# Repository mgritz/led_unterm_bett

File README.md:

# led_unterm_bett
PCB for ESP8266-based LED Low-Lights Controller

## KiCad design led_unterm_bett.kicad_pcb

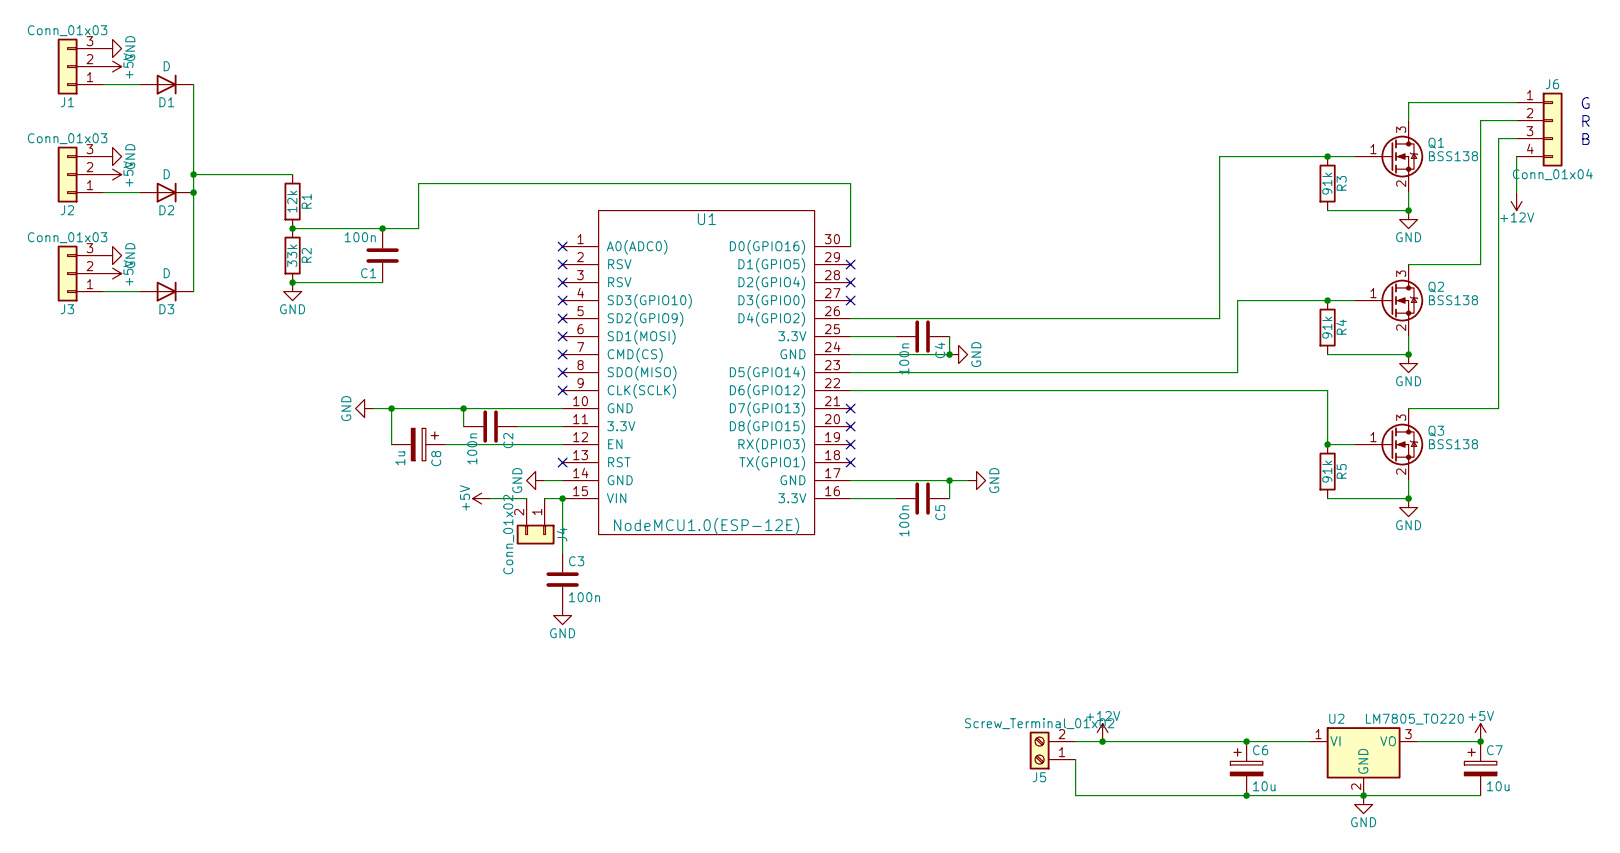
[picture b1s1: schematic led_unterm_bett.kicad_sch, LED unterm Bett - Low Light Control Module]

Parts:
C1, C2, C3, C4, C5: 100n; C_0805_HandSoldering
C6, C7: 10u; CP_Radial_D10.0mm_P3.50mm
C8: 1u; CP_Radial_D10.0mm_P3.50mm
D1, D2, D3: D; D_MiniMELF_Handsoldering
J1, J2, J3: Conn_01x03; Pin_Header_Straight_1x03_Pitch2.54mm
J4: Conn_01x02; Pin_Header_Straight_1x02_Pitch2.54mm
J5: Screw_Terminal_01x02; TerminalBlock_bornier-2_P5.08mm
J6: Conn_01x04; Pin_Header_Straight_1x04_Pitch2.54mm
Q1, Q2, Q3: BSS138; SOT-23
R1: 12k; R_0805_HandSoldering
R2: 33k; R_0805_HandSoldering
R3, R4, R5: 91k; R_0805_HandSoldering
U1: NodeMCU1.0(ESP-12E); ESP12F-Devkit-V3
U2: LM7805_TO220; TO-220-3_Vertical

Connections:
+5V: C7.1, J1.2, J2.2, J3.2, J4.2, U2.3 (VO)
+12V: C6.1, J5.2, J6.4, U2.1 (VI)
GND: C1.1, C2.2, C3.2, C4.1, C5.1, C6.2, C7.2, C8.2, J1.3, J2.3, J3.3, J5.1, Q1.2 (S), Q2.2 (S), Q3.2 (S), R2.2, R3.2, R4.2, R5.2, U1.10 (GND), U1.14 (GND), U1.17 (GND), U1.24 (GND), U2.2 (GND)
unnamed: C1.2, R1.2, R2.1, U1.30 (D0(GPIO16))
unnamed: C2.1, U1.11 (3.3V)
unnamed: C3.1, J4.1, U1.15 (VIN)
unnamed: C4.2, U1.25 (3.3V)
unnamed: C5.2, U1.16 (3.3V)
unnamed: C8.1, U1.12 (EN)
unnamed: D1.1 (K), D2.1 (K), D3.1 (K), R1.1
unnamed: D1.2 (A), J1.1
unnamed: D2.2 (A), J2.1
unnamed: D3.2 (A), J3.1
unnamed: J6.1, Q1.3 (D)
unnamed: J6.2, Q2.3 (D)
unnamed: J6.3, Q3.3 (D)
unnamed: Q1.1 (G), R3.1, U1.26 (D4(GPIO2))
unnamed: Q2.1 (G), R4.1, U1.23 (D5(GPIO14))
unnamed: Q3.1 (G), R5.1, U1.22 (D6(GPIO12))

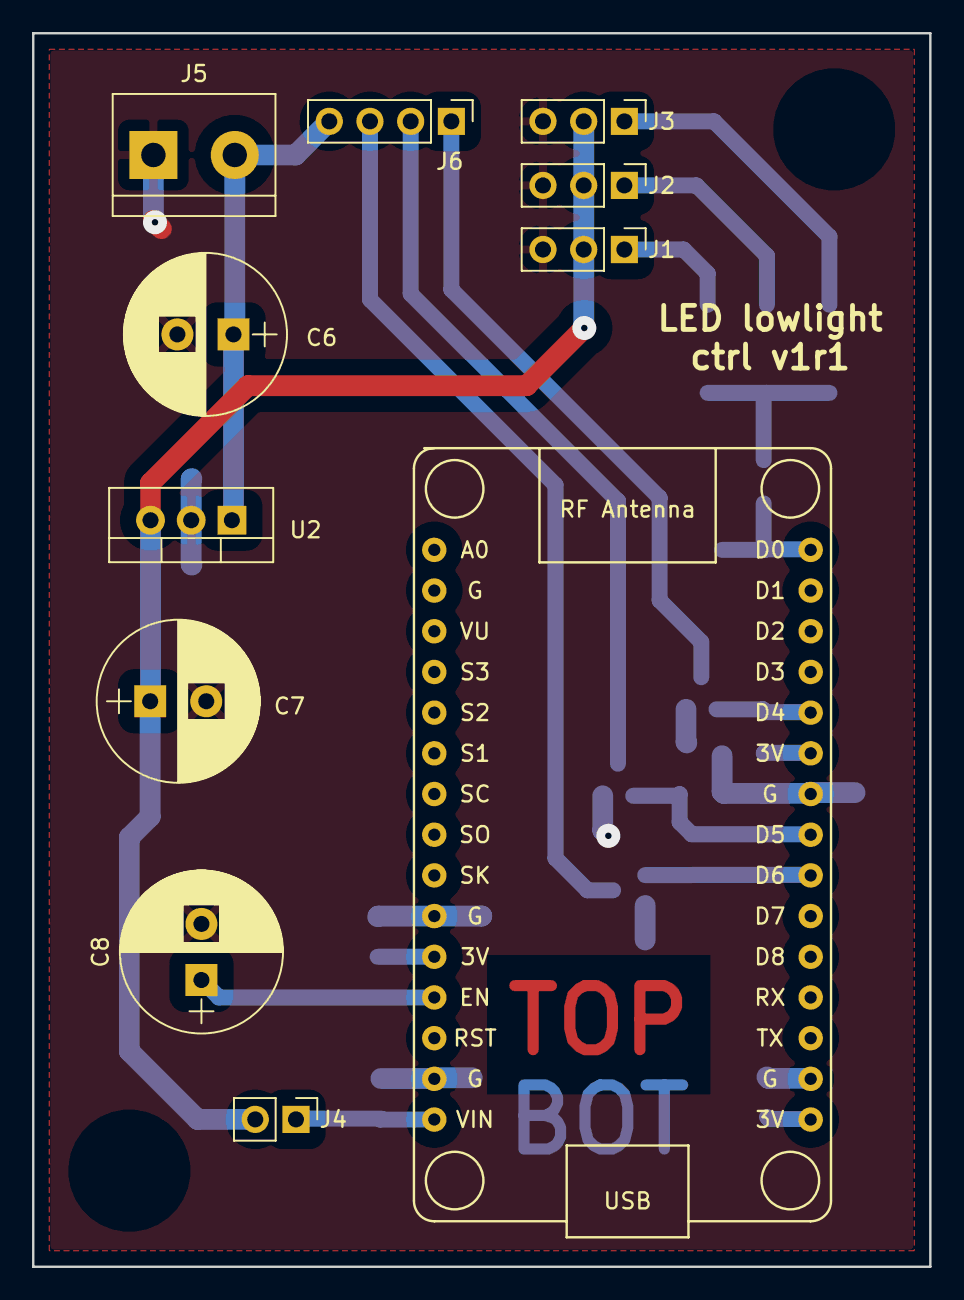
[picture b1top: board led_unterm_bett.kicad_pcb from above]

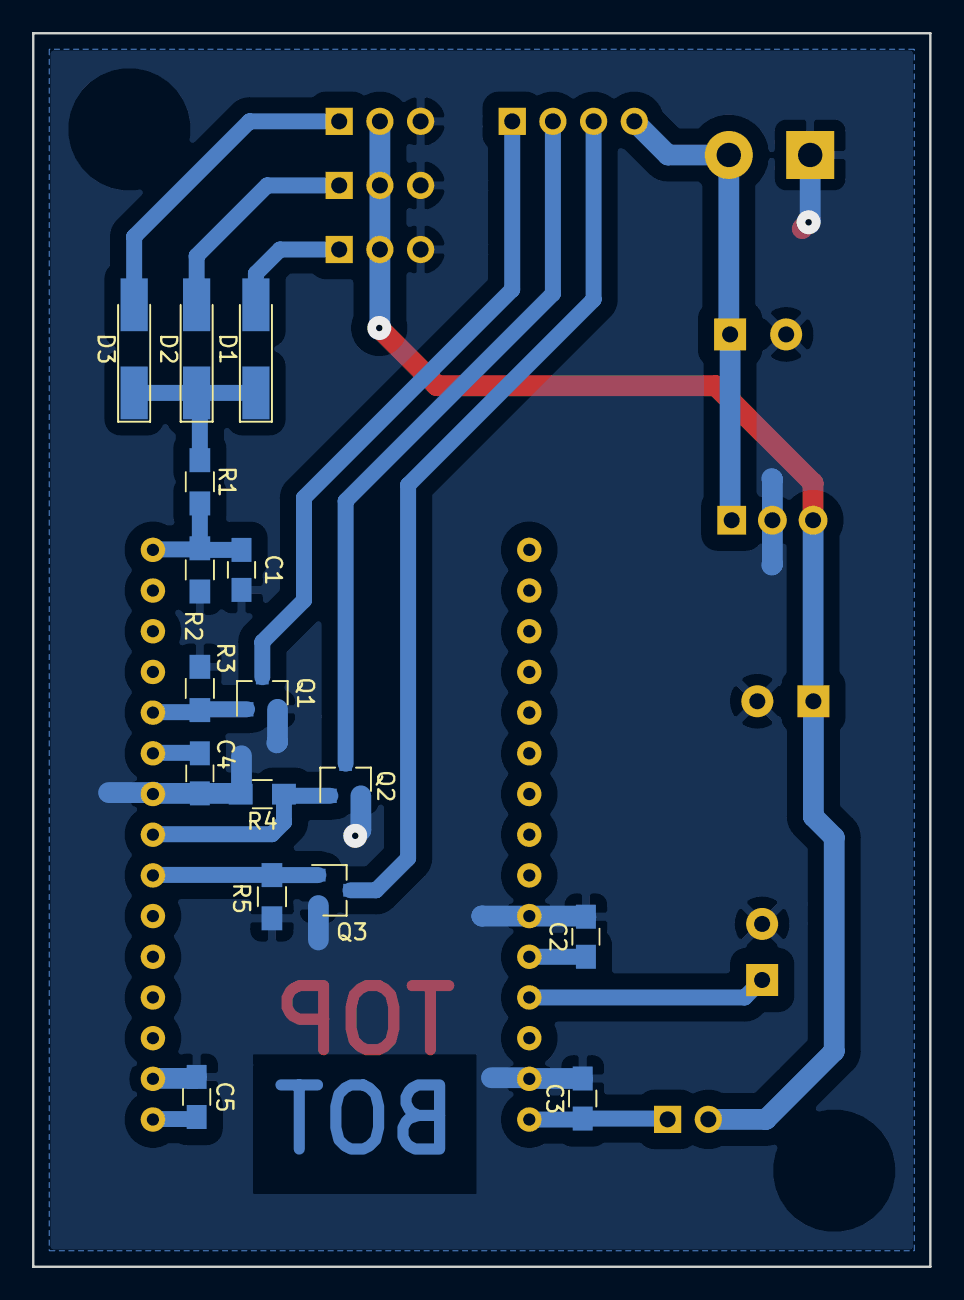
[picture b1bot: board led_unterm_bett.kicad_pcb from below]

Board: 2 copper layers, 56.0 x 77.0 mm, 27 parts (16 on the bottom side), 19 nets.

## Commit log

2020-11-15 initial schematic idea
    No pcb yet and there are changes pending from experimenting a bit around...
2020-12-12 finish schematic and devise netlist
    ready start routing
2020-12-12 placement complete
2020-12-12 finish routing for etched PCB
2020-12-12 etching artifacts for v1r1 manufacturing
2021-01-31 kicad 4->5, jlcpcb drc
    Load design rules from https://github.com/sethhillbrand/kicad_templates.
    Used rules for jlcpcb.com
2021-12-22 shrink board and add mounting holes
2021-12-22 add outjob exports (gerber)
2021-12-22 gitignore: rescue-backup
2022-01-06 migrate to kicad 6.0
2022-01-06 update some resistor values
    so the 0805er E-series set lasts longer ;-)
2022-02-12 add HC-SR501 pinout and audio jack wiring to schematic
2022-02-12 add case freecad design as printed
